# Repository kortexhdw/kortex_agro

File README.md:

Kortex AGRO open-source board files, enjoy!

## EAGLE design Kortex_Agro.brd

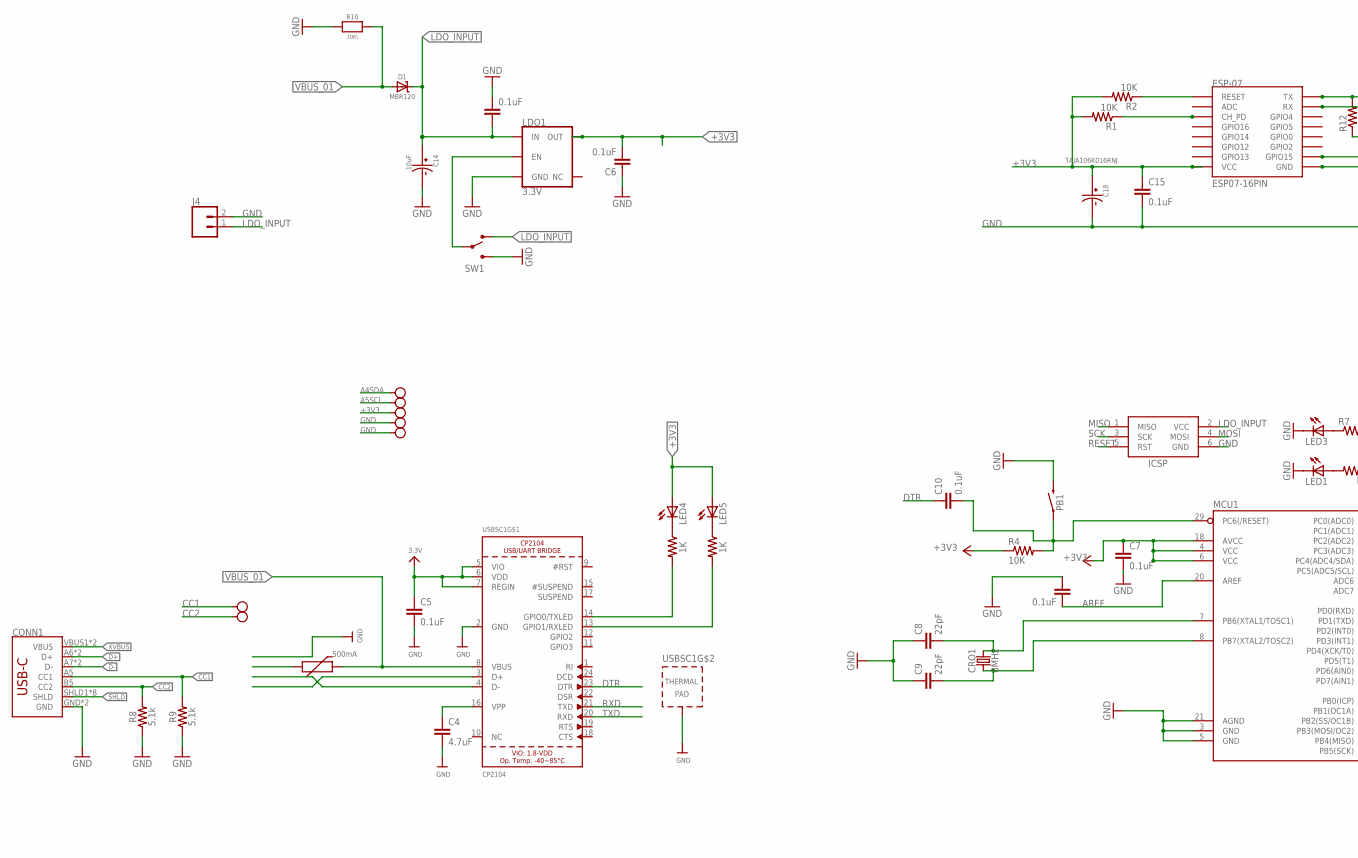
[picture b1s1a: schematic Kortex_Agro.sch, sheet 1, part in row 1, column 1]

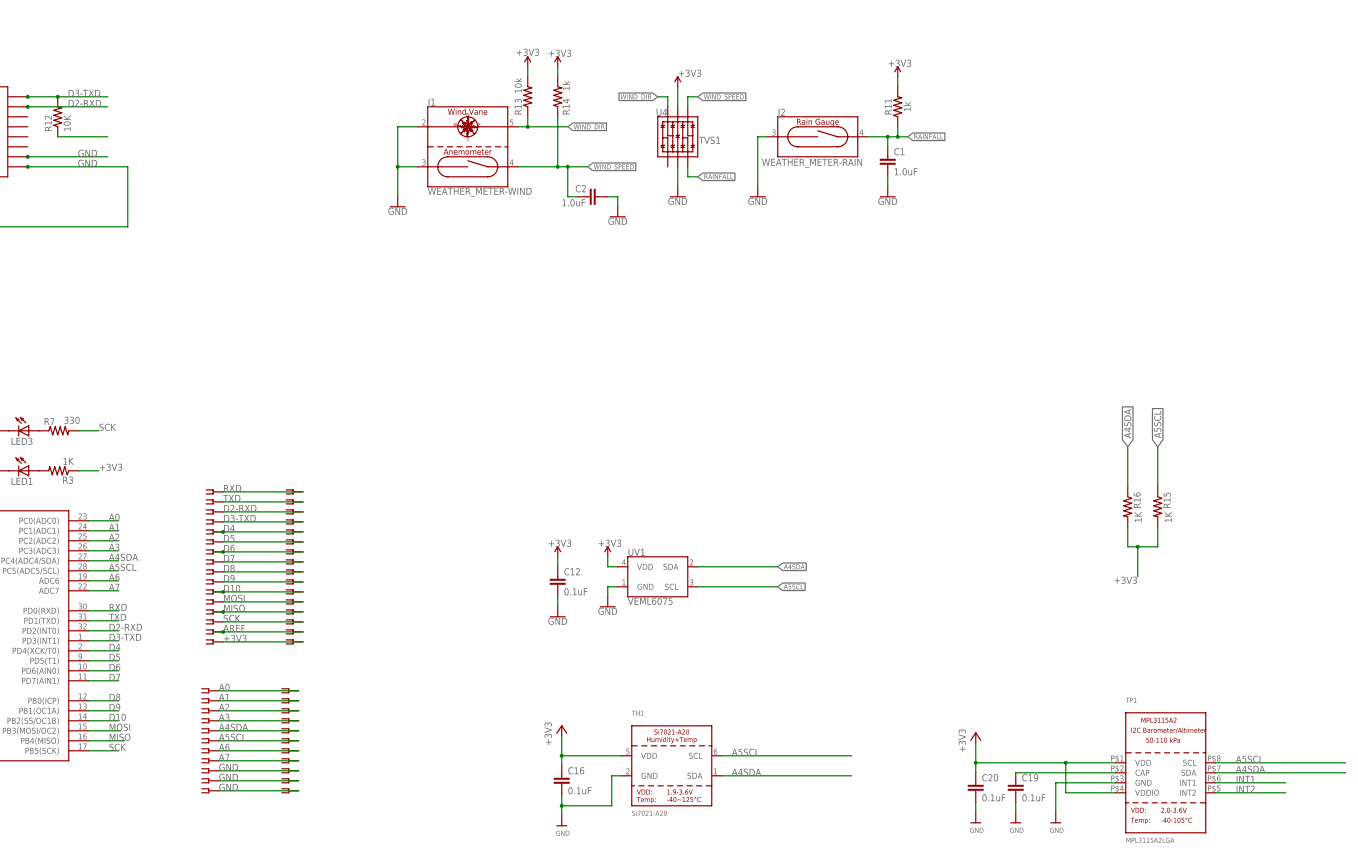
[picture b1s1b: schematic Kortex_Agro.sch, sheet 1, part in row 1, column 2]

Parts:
+3.3V: +3V3; TP-D45MIL
C1, C2: 1.0uF; 0603
C3, C5, C6, C7, C10, C11, C15, C16, C19, C20: 0.1uF; 0805
C4: 4.7uF; 0805
C8, C9: 22pF; 0805
C12: 0.1uF; 0603
C14: 10uF; CAPMP3216X166
C18: TAJA106K016RNJ; CAPMP3216X166
CONN1: USB_C16PIN; USB-C-16P
CRO1: 8MHz; CRYSTAL-SMD-5X3.2-4PAD
D1: MBR120; SOD-123
ESP-07: ESP07-16PIN
GND, GND13, GND21, GND22: GND; TP-D45MIL
HD1: SSW-116-02-G-D
HD2: SSW-111-02-S-D
ICSP: AVRISP-6; AVRISP
J1: WEATHER_METER-WIND; RJ11-6
J2: WEATHER_METER-RAIN; RJ11-6
J4: CONN_02; 1X02
LDO1: 3.3V; SOT23-5
LED1, LED3, LED4, LED5: LEDCHIPLED_0805; CHIPLED_0805
MCU1: ATMEGA328P_TQFPATMEGA328P-AU; QFP80P912X912X120-32
PB1: SWITCH-MOMENTARY-2SMD; TACTILE_SWITCH_SMD
PTC1: 500mA; PTC-1206
R1, R2, R4, R12: 10K; M0805
R3, R5, R6, R15, R16: 1K; M0805
R7: 330; M0805
R8, R9: 5.1k; 0603
R10: 10K\; 0805-NO
R11, R14: 1k; 0603
R13: 10k; 0603
SCL: SCL; TP-D45MIL
SDA: SDA; TP-D45MIL
SW1: SWITCH-SPSTSMD; AYZ0202
TH1: Si7021-A20; DFN6_3X3_SI
TP1: MPL3115A2LGA; LGA8
U4: TVS1; SOT-23-6
USBSC1: CP2104; QFN24_4MM_SMSC
UV1: VEML6075; VEML6075_A3OP

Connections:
+3V3: +3.3V.T, C5.1, C6.2, C7.1, C12.1, C15.1, C16.1, C18.+, C20.1, ESP-07.VCC, HD1.31, HD1.32, LDO1.5 (OUT), LED4.A, LED5.A, MCU1.4 (VCC), MCU1.6 (VCC), MCU1.18 (AVCC), R1.2, R2.2, R3.1, R4.1, R11.2, R13.2, R14.2, R15.2, R16.2, TH1.5 (VDD), TP1.P$1 (VDD), TP1.P$4 (VDDIO), U4.5 (VCC), USBSC1.5 (VIO), USBSC1.6 (VDD), USBSC1.7 (REGIN), UV1.4 (VDD)
A0: HD2.1, HD2.2, MCU1.23 (PC0(ADC0))
A1: HD2.3, HD2.4, MCU1.24 (PC1(ADC1))
A2: HD2.5, HD2.6, MCU1.25 (PC2(ADC2))
A3: HD2.7, HD2.8, MCU1.26 (PC3(ADC3))
A4SDA: HD2.9, HD2.10, MCU1.27 (PC4(ADC4/SDA)), R16.1, SDA.T, TH1.1 (SDA), TP1.P$7 (SDA), UV1.2 (SDA)
A5SCL: HD2.11, HD2.12, MCU1.28 (PC5(ADC5/SCL)), R15.1, SCL.T, TH1.6 (SCL), TP1.P$8 (SCL), UV1.3 (SCL)
A6: HD2.13, HD2.14, MCU1.19 (ADC6)
A7: HD2.15, HD2.16, MCU1.22 (ADC7)
AREF: C11.2, HD1.29, HD1.30, MCU1.20 (AREF)
CAP1: C19.1, TP1.P$2 (CAP)
CC1: CONN1.A5 (CC1), GND21.T, R9.2
CC2: CONN1.B5 (CC2), GND22.T, R8.2
D2-RXD: ESP-07.RX, HD1.5, HD1.6, MCU1.32 (PD2(INT0))
D3-TXD: ESP-07.TX, HD1.7, HD1.8, MCU1.1 (PD3(INT1)), R12.2
D4: HD1.9, HD1.10, MCU1.2 (PD4(XCK/T0))
D5: HD1.11, HD1.12, MCU1.9 (PD5(T1))
D6: HD1.13, HD1.14, MCU1.10 (PD6(AIN0))
D7: HD1.15, HD1.16, MCU1.11 (PD7(AIN1))
D8: HD1.17, HD1.18, MCU1.12 (PB0(ICP))
D9: HD1.19, HD1.20, MCU1.13 (PB1(OC1A))
D10: HD1.21, HD1.22, MCU1.14 (PB2(SS/OC1B))
D+: CONN1.A6 (D+), CONN1.B6 (D+), USBSC1.3 (D+)
D-: CONN1.A7 (D-), CONN1.B7 (D-), USBSC1.4 (D-)
DTR: C10.1, USBSC1.23 (DTR)
GND: C1.2, C2.2, C3.1, C4.2, C5.2, C6.1, C7.2, C8.1, C9.1, C11.1, C12.2, C14.-, C15.2, C16.2, C18.-, C19.2, C20.2, CONN1.GND, CONN1.GND2 (GND), ESP-07.GND, ESP-07.GPIO15, GND.T, GND13.T, HD2.17, HD2.18, HD2.19, HD2.20, HD2.21, HD2.22, ICSP.6 (GND), J1.2 (DIR-1), J1.3 (ANN-1), J2.3 (1), J4.2, LDO1.2 (GND), LED1.C, LED3.C, MCU1.3 (GND), MCU1.5 (GND), MCU1.21 (AGND), PB1.3 (2), R8.1, R9.1, R10.1, SW1.3 (S), TH1.2 (GND), TP1.P$3 (GND), U4.2 (VSS), USBSC1.2 (GND), USBSC1.THERM (TP), UV1.1 (GND)
GPIO/0: R6.2, USBSC1.14 (GPIO0/TXLED)
GPIO/1: R5.2, USBSC1.13 (GPIO1/RXLED)
INT1: TP1.P$6 (INT1)
INT2: TP1.P$5 (INT2)
LDO_INPUT: C3.2, C14.+, D1.C, ICSP.2 (VCC), J4.1, LDO1.1 (IN), SW1.1 (O)
MISO: HD1.25, HD1.26, ICSP.1 (MISO), MCU1.16 (PB4(MISO))
MOSI: HD1.23, HD1.24, ICSP.4 (MOSI), MCU1.15 (PB3(MOSI/OC2))
unnamed: LED3.A, R7.1
unnamed: LED1.A, R3.2
unnamed: ESP-07.CH_PD, R1.1
unnamed: LED4.C, R6.1
unnamed: C9.2, CRO1.1, MCU1.8 (PB7(XTAL2/TOSC2))
unnamed: C8.2, CRO1.3 (2), MCU1.7 (PB6(XTAL1/TOSC1))
unnamed: LED5.C, R5.1
unnamed: ESP-07.REST (RESET), R2.1
unnamed: C4.1, USBSC1.16 (VPP)
unnamed: LDO1.3 (EN), SW1.2
PPP: R12.1
RAINFALL: C1.1, J2.4 (2), R11.1, U4.3 (IO2)
RESET: C10.2, ICSP.5 (RST), MCU1.29 (PC6(/RESET)), PB1.1, R4.2
RXD: HD1.1, HD1.2, MCU1.30 (PD0(RXD)), USBSC1.21 (TXD)
SCK: HD1.27, HD1.28, ICSP.3 (SCK), MCU1.17 (PB5(SCK)), R7.2
SHLD: CONN1.SHLD1 (SHLD), CONN1.SHLD2 (SHLD), CONN1.SHLD3 (SHLD), CONN1.SHLD4 (SHLD), CONN1.SHLD5 (SHLD), CONN1.SHLD6 (SHLD), CONN1.SHLD7 (SHLD), CONN1.SHLD8 (SHLD)
TXD: HD1.3, HD1.4, MCU1.31 (PD1(TXD)), USBSC1.20 (RXD)
VBUS_01: D1.A, PTC1.2, R10.2, USBSC1.8 (VBUS)
WIND_DIR: J1.5 (DIR2), R13.1, U4.6 (IO4)
WIND_SPEED: C2.1, J1.4 (ANN-2), R14.1, U4.4 (IO3)
XVBUS: CONN1.VBUS1 (VBUS), CONN1.VBUS2 (VBUS), PTC1.1

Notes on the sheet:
500mA

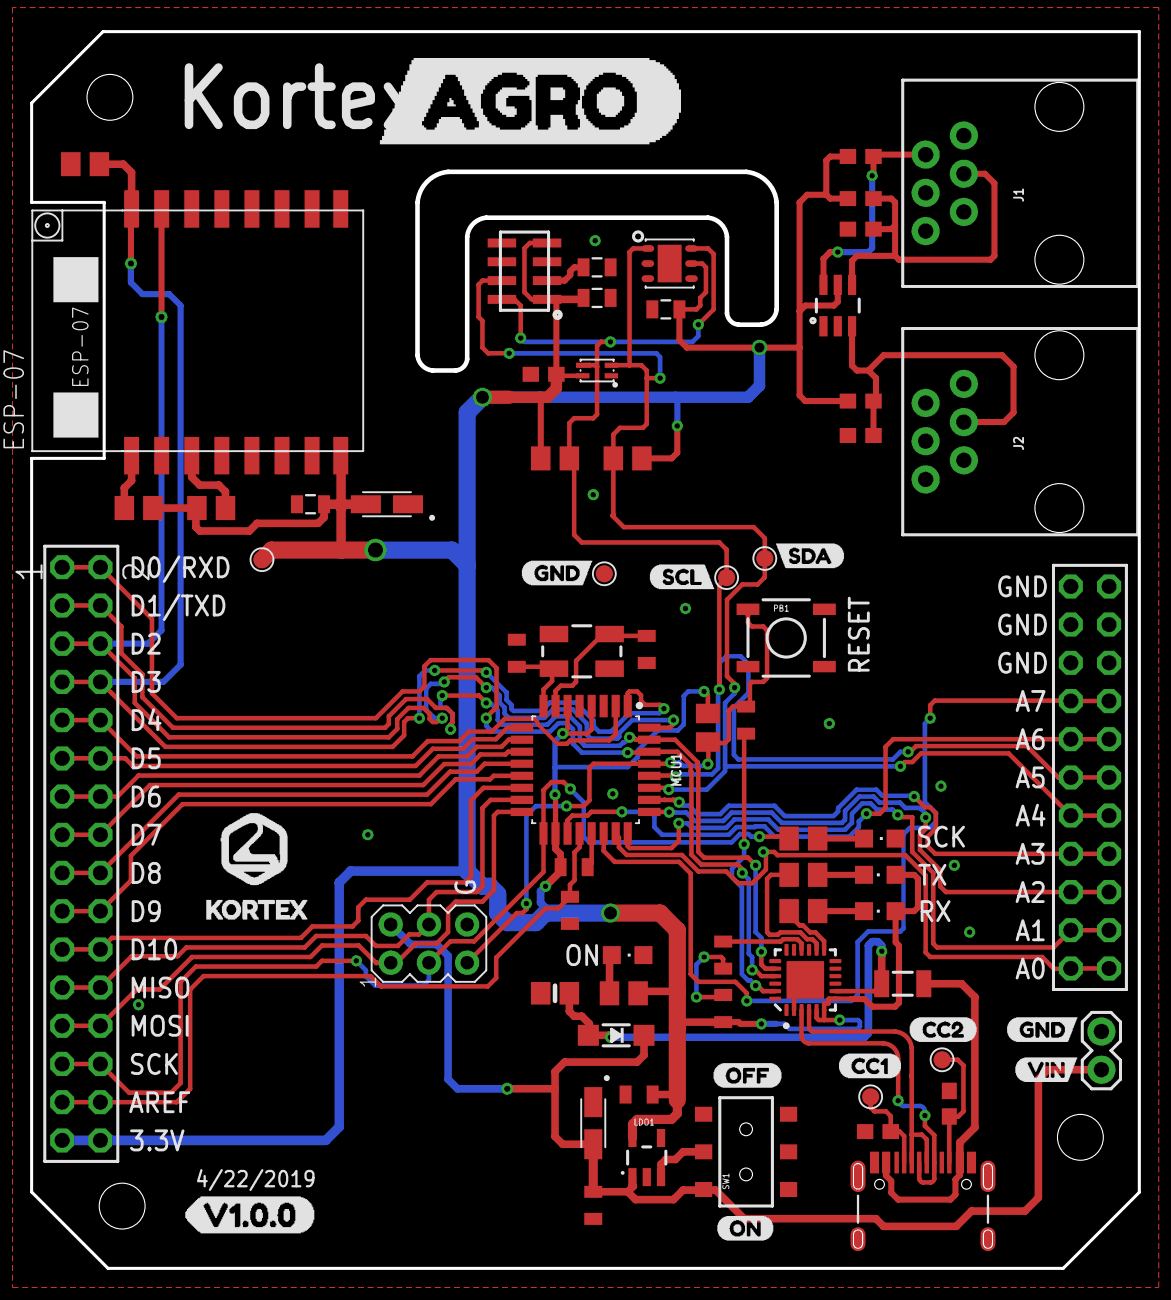
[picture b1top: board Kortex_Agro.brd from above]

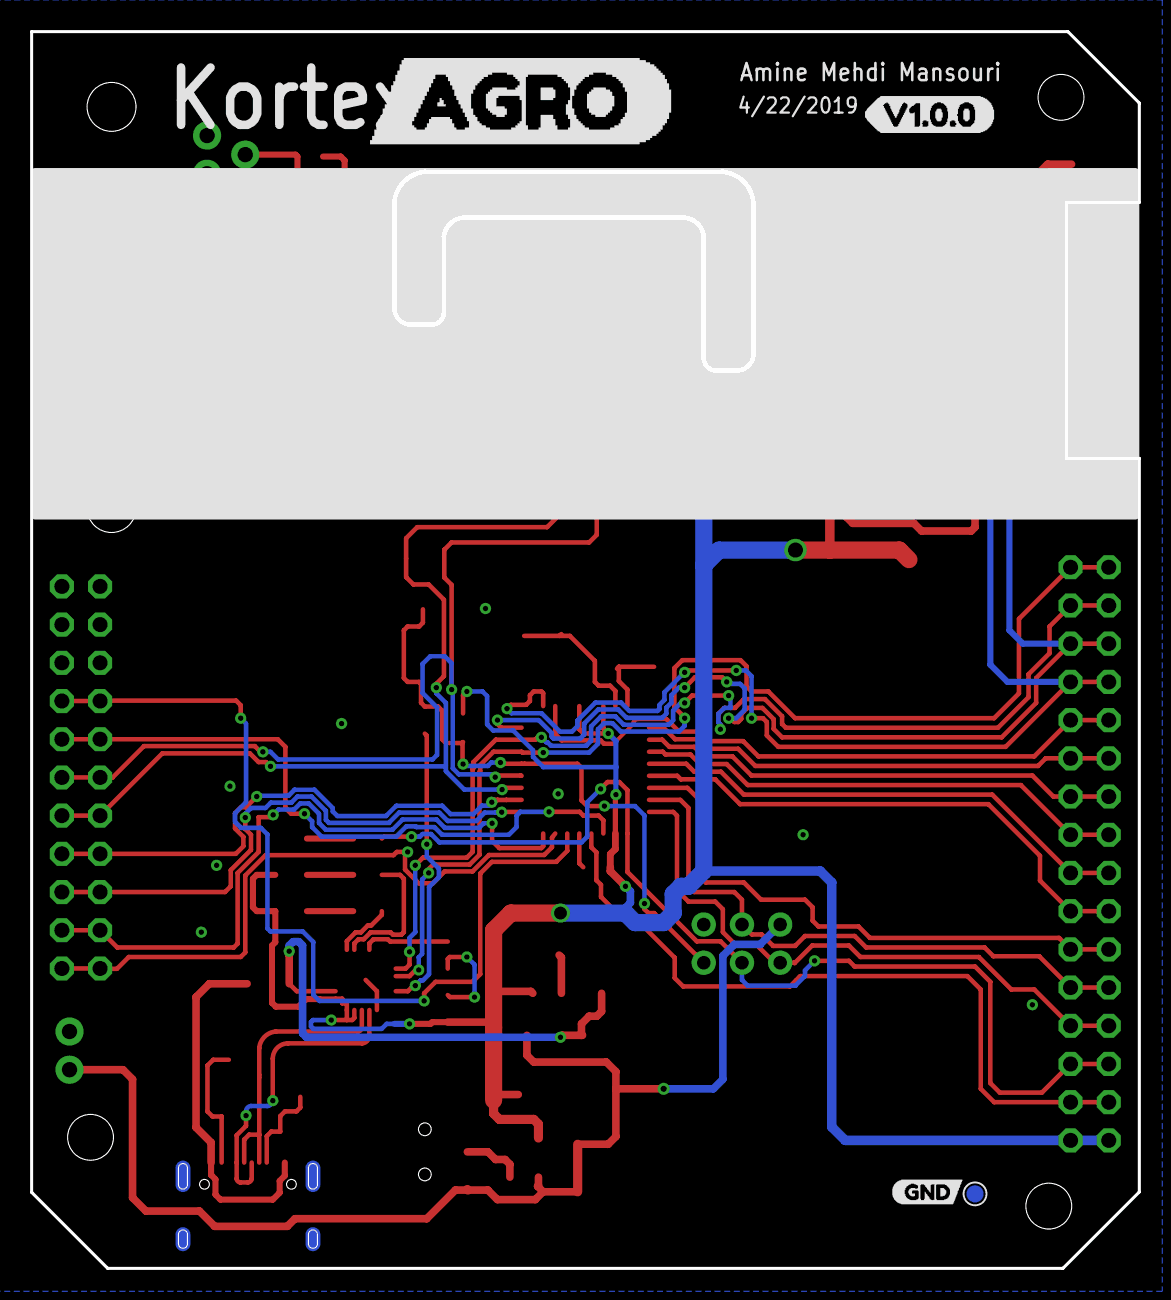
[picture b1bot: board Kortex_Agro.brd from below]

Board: 2 copper layers, 73.6 x 82.2 mm, 80 parts (4 on the bottom side), 51 nets.

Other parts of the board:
U$1, U$2, U$17: GND0
U$3: SCL0
U$4: SDA0
U$7: CC10
U$8: CC20
U$9: ON0
U$10: OFF0
U$11, U$13: V1#0#00
U$12, U$14: AGRO0
U$18: VIN0
U$20: KORTEX_BIG_01#PNG

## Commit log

2019-07-18 Deleted Gerber/DrillFiles/drills.xln
2019-07-18 Deleted Gerber/GerberFiles/copper_bottom.gbr
2019-07-18 Deleted Gerber/GerberFiles/copper_top.gbr
2019-07-18 Deleted Gerber/GerberFiles/gerber_job.gbrjob
2019-07-18 Deleted Gerber/GerberFiles/profile.gbr
2019-07-18 Deleted Gerber/GerberFiles/silkscreen_bottom.gbr
2019-07-18 Deleted Gerber/GerberFiles/silkscreen_top.gbr
2019-07-18 Deleted Gerber/GerberFiles/soldermask_bottom.gbr
2019-07-18 Deleted Gerber/GerberFiles/soldermask_top.gbr
2019-07-18 Deleted Gerber/GerberFiles/solderpaste_bottom.gbr
2019-07-18 Deleted Gerber/GerberFiles/solderpaste_top.gbr
2019-07-18 Deleted Partslist/partslist
2019-07-18 Deleted Kortex_A2-B.b#1
2019-07-18 Deleted Kortex_A2-B.b#2
2019-07-18 Deleted Kortex_A2-B.b#3
2019-07-18 Deleted Kortex_A2-B.b#4
2019-07-18 Deleted Kortex_A2-B.b#5
2019-07-18 Deleted Kortex_A2-B.b#6
2019-07-18 Deleted Kortex_A2-B.b#7
2019-07-18 Deleted Kortex_A2-B.b#8
2019-07-18 Deleted Kortex_A2-B.b#9
2019-07-18 Deleted Kortex_A2-B.s#1
2019-07-18 Deleted Kortex_A2-B.s#2
2019-07-18 Deleted Kortex_A2-B.s#3
2019-07-18 Deleted Kortex_A2-B.s#4
2019-07-18 Deleted Kortex_A2-B.s#5
2019-07-18 Deleted Kortex_A2-B.s#6
2019-07-18 Deleted Kortex_A2-B.s#7
2019-07-18 Deleted Kortex_A2-B.s#8
2019-07-18 Deleted Kortex_A2-B.s#9
2019-07-18 Deleted Kortex_A2_Lite.b#1
2019-07-18 Deleted Kortex_A2_Lite.b#2
2019-07-18 Deleted Kortex_A2_Lite.b#3
2019-07-18 Deleted Kortex_A2_Lite.b#4
2019-07-18 Deleted Kortex_A2_Lite.b#5
2019-07-18 Deleted Kortex_A2_Lite.b#6
2019-07-18 Deleted Kortex_A2_Lite.b#7
2019-07-18 Deleted Kortex_A2_Lite.b#8
2019-07-18 Deleted Kortex_A2_Lite.b#9
2019-07-18 Deleted Kortex_A2_Lite.s#1
2019-07-18 Deleted Kortex_A2_Lite.s#2
2019-07-18 Deleted Kortex_A2_Lite.s#3
2019-07-18 Deleted Kortex_A2_Lite.s#4
2019-07-18 Deleted Kortex_A2_Lite.s#5
2019-07-18 Deleted Kortex_A2_Lite.s#6
2019-07-18 Deleted Kortex_A2_Lite.s#7
2019-07-18 Deleted Kortex_Agro.b#1
2019-07-18 Deleted Kortex_Agro.b#2
2019-07-18 Deleted Kortex_Agro.b#3
2019-07-18 Deleted Kortex_Agro.b#4
2019-07-18 Deleted Kortex_Agro.b#5
2019-07-18 Deleted Kortex_Agro.b#6
2019-07-18 Deleted Kortex_Agro.b#7
2019-07-18 Deleted Kortex_Agro.b#8
2019-07-18 Deleted Kortex_Agro.b#9
2019-07-18 Deleted Kortex_Agro.s#1
2019-07-18 Deleted Kortex_Agro.s#2
2019-07-18 Deleted Kortex_Agro.s#3
2019-07-18 Deleted Kortex_Agro.s#4
2019-07-18 Deleted Kortex_Agro.s#5
2019-07-18 Deleted Kortex_Agro.s#6
2019-07-18 Deleted Kortex_Agro.s#7
2019-07-18 Deleted Kortex_Agro.s#8
2019-07-18 Deleted Kortex_Agro.s#9
2019-07-18 Created LICENSE
2019-07-18 Added Dimensions folder and Images folder

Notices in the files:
parts and their libraries:
SparkFun: Licensing: CC v3.0 Share-Alike You are welcome to use this library for commercial purposes.
SparkFun-Clocks: Licensing: Creative Commons ShareAlike 4.0 International - https://creativecommons.org/licenses/by-sa/4.0
